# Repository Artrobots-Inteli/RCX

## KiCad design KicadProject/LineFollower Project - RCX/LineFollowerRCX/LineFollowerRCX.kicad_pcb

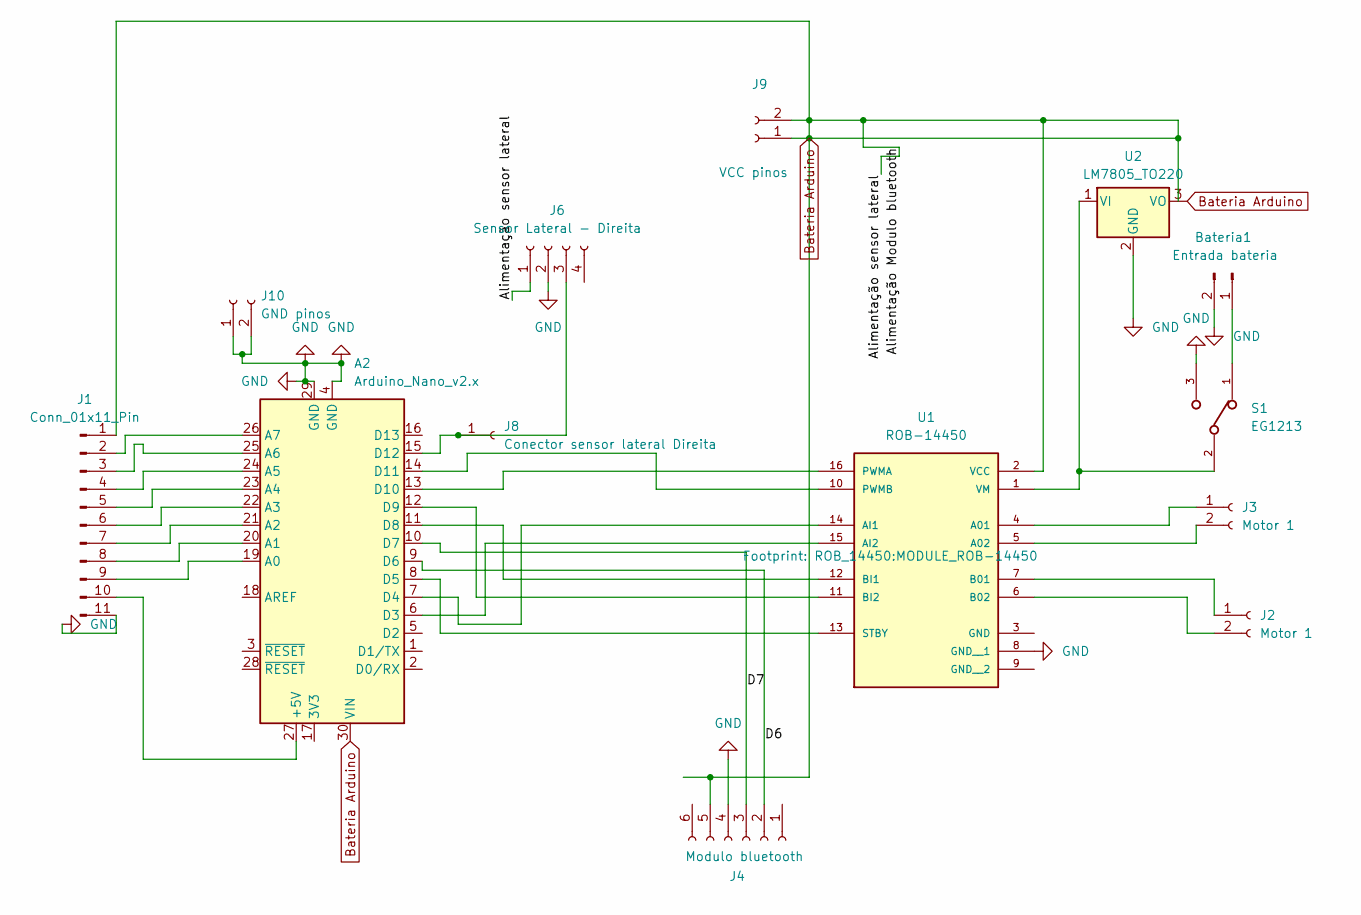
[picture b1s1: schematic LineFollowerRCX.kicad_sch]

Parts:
A2: Arduino_Nano_v2.x; Arduino_Nano
Bateria1: Entrada bateria; PinSocket_1x02_P2.54mm_Vertical
J1: Conn_01x11_Pin; PinSocket_1x11_P2.54mm_Vertical
J2, J3: Motor 1; PinSocket_1x02_P2.54mm_Vertical
J4: Modulo bluetooth; PinSocket_1x06_P2.54mm_Vertical
J6: Sensor Lateral - Direita; PinSocket_1x04_P2.54mm_Horizontal
J8: Conector sensor lateral Direita; PinSocket_1x01_P2.54mm_Vertical
J9: VCC pinos; PinSocket_1x02_P2.54mm_Vertical
J10: GND pinos; PinSocket_1x02_P2.54mm_Vertical
S1: EG1213; SW_EG1213
U1: ROB-14450; MODULE_ROB-14450; PARTREV 11-13-17
U2: LM7805_TO220; TO-220-3_Vertical

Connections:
/D6: A2.9 (D6), J4.2 (RX)
/D7: A2.10 (D7), J4.3 (TX)
Bateria Arduino: A2.30 (VIN), J1.1, J4.5 (VCC), J6.1 (VCC), J9.1, J9.2, U1.2 (VCC), U2.3 (VO)
GND: A2.4 (GND), A2.29 (GND), Bateria1.2 (-), J1.11, J4.4 (GND), J6.2 (GND), J10.1, J10.2, S1.3, U1.8 (GND__1), U2.2 (GND)
unnamed: A2.27 (+5V), J1.10
unnamed: A2.19 (A0), J1.9
unnamed: A2.20 (A1), J1.8
unnamed: A2.21 (A2), J1.7
unnamed: A2.22 (A3), J1.6
unnamed: A2.23 (A4), J1.5
unnamed: A2.24 (A5), J1.4
unnamed: A2.25 (A6), J1.3
unnamed: A2.26 (A7), J1.2
unnamed: A2.6 (D3), U1.15 (AI2)
unnamed: A2.7 (D4), U1.14 (AI1)
unnamed: A2.8 (D5), U1.13 (STBY)
unnamed: A2.11 (D8), U1.12 (BI1)
unnamed: A2.12 (D9), U1.11 (BI2)
unnamed: A2.13 (D10), U1.16 (PWMA)
unnamed: A2.14 (D11), U1.10 (PWMB)
unnamed: A2.15 (D12), J6.3 (D0), J8.1
unnamed: Bateria1.1 (+), S1.1
unnamed: J2.1 (+), U1.7 (B01)
unnamed: J2.2 (-), U1.6 (B02)
unnamed: J3.1 (+), U1.4 (A01)
unnamed: J3.2 (-), U1.5 (A02)
unnamed: S1.2, U1.1 (VM), U2.1 (VI)

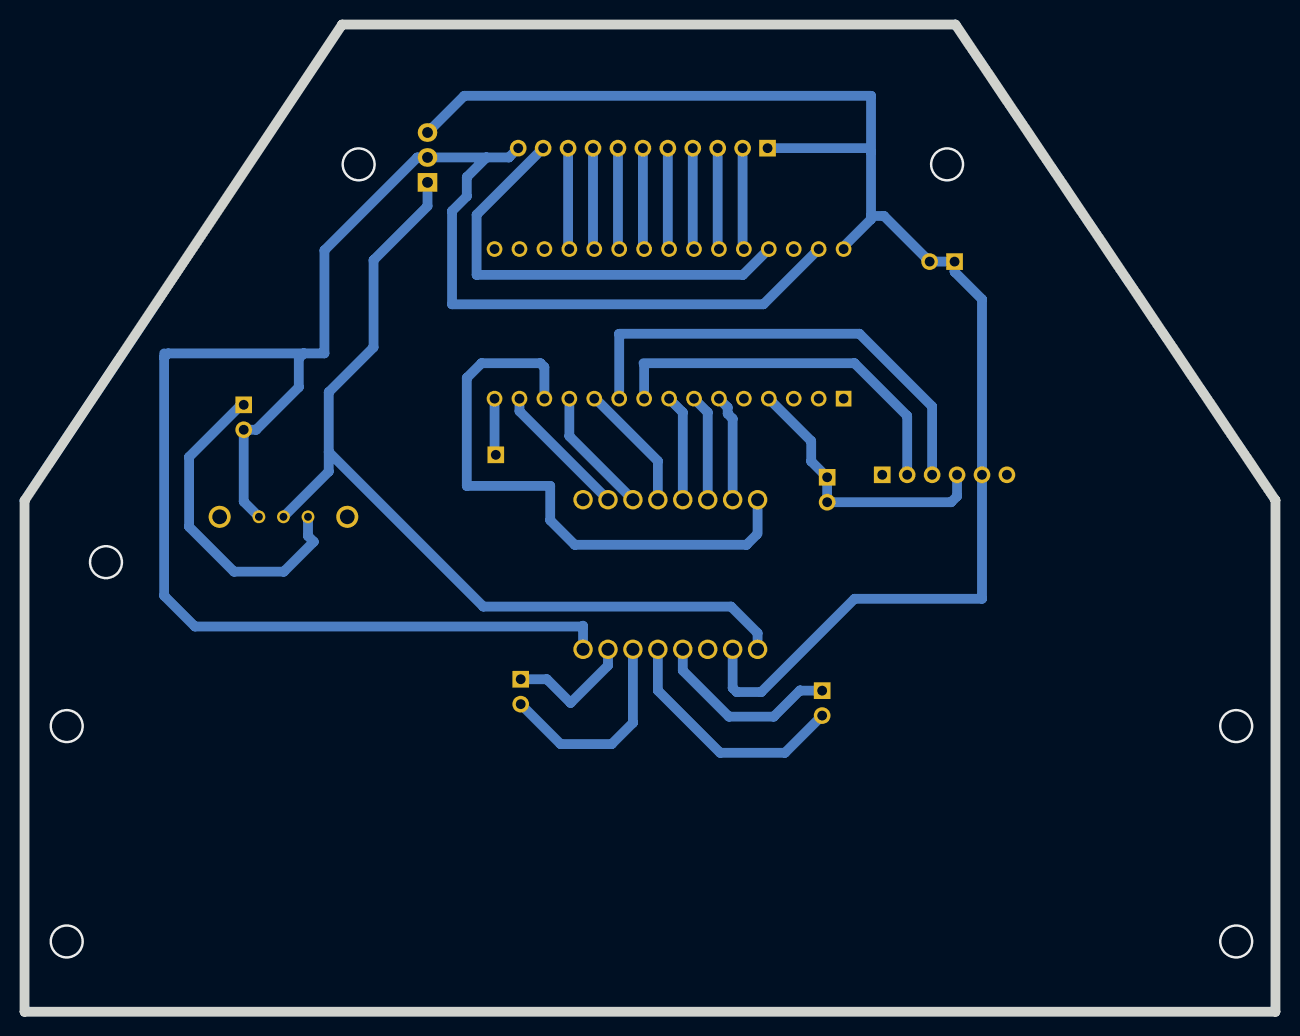
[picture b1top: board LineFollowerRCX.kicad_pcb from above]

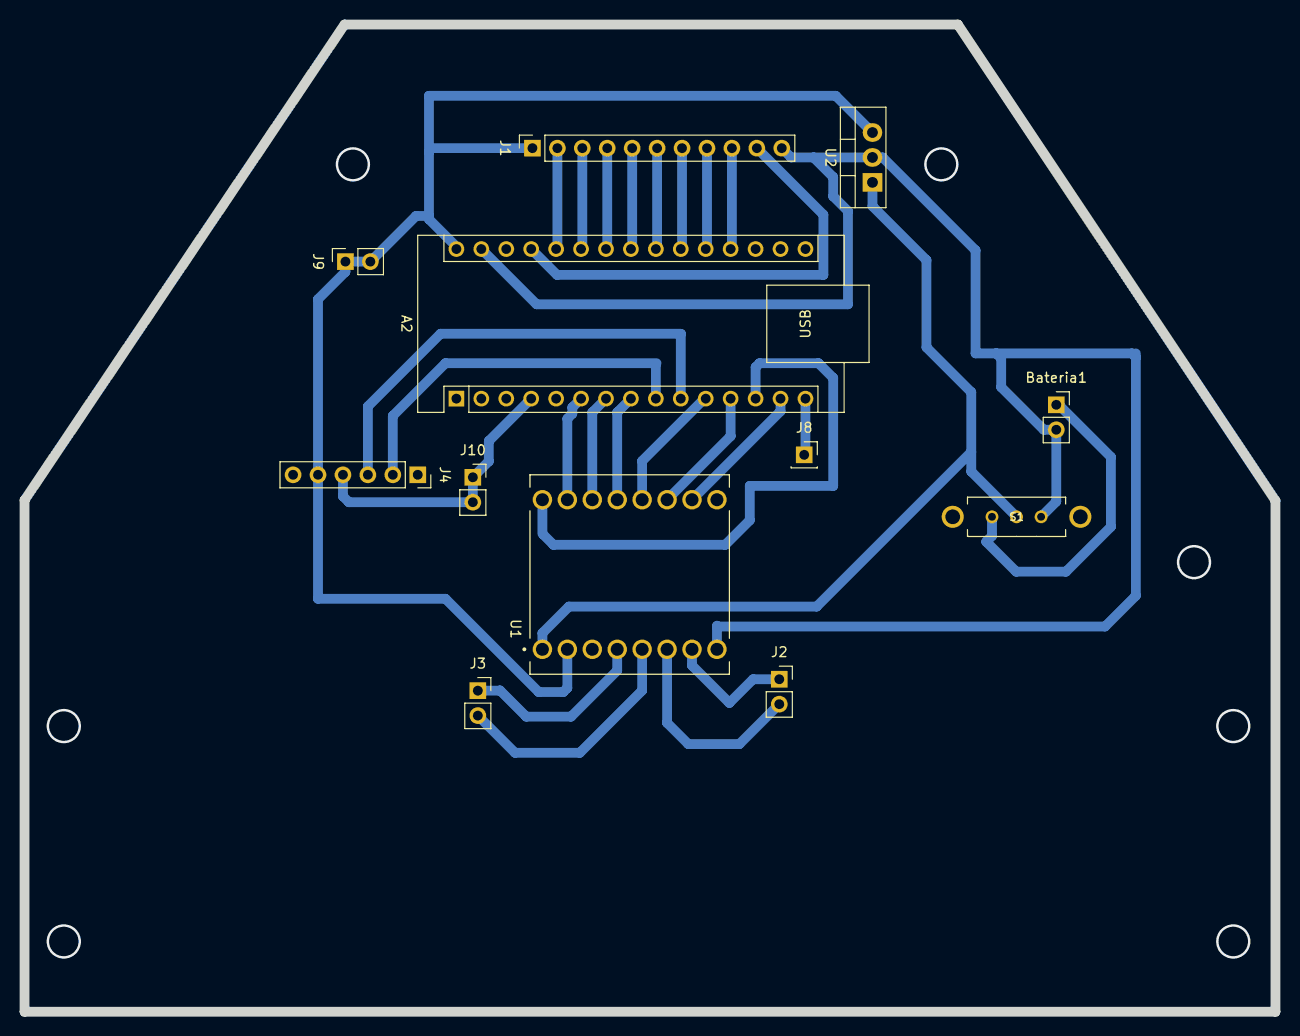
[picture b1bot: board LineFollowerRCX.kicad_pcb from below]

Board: 2 copper layers, 127.4 x 100.6 mm, 12 parts (12 on the bottom side), 27 nets.

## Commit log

2024-05-21 Códigos de estudo para o seguidor de linha
2024-06-12 Projeto Kicad
2024-06-20 Novo design de PCB e arquivos gebers e de furação
2024-06-20 Arrumando design
2024-07-09 Codigos de teste e pcb invertida
2024-07-10 Pequenas alterações no projeto Kicad
2024-07-10 adding h bridge test code
2024-07-11 Mais testes ponte H
2024-07-12 testes com os sensores
2024-07-12 QTRA Exempla
2024-07-12 adicionando o pino de IR
2024-07-13 Primeiro teste para com sensores e movimentação
2024-07-13 Teste com PID relativamente funcional
2024-07-13 TestePDI2 tá começando a ficar confiavel
2024-07-13 Teste PDI + QRTsensors
2024-07-13 Infelizmente não foi :(
2024-08-24 feat: remove sensor lateral esquerdo e aumenta tamanho da placa para suportar bateria
2024-08-24 fix: remove sensor lateral esquerdo do esquemático
2024-09-10 altera dimensões da placa & ajusta posições dos componentes
2024-09-15 novos testes
2024-09-15 tete
2024-09-17 fix; arrumando corte da placa
2024-09-25 fix: troca porta PWMA da ponte h para pino 10
2024-09-27 fix: arrumando espaçãmento da bateria robô
2024-09-30 fix: ajusta pinos de alimentacao da ponte h e sensores
2024-09-30 tirando marcacoes e virando a placa
2024-09-30 arquivos gebers e furacao
2024-10-05 feat: all codigos novos do novo robo (seguindo linha)
2024-10-11 feat: ajusta as constantes do pid
2024-10-11 feat: robo seguindo, bençaos maravilhosas
2024-10-12 feat: coisinhas pro motor de 3000
2024-10-12 feat: codigo robo lib qrt
2024-10-12 feat: benção maravilhosas: funcionando com 3000rpm
